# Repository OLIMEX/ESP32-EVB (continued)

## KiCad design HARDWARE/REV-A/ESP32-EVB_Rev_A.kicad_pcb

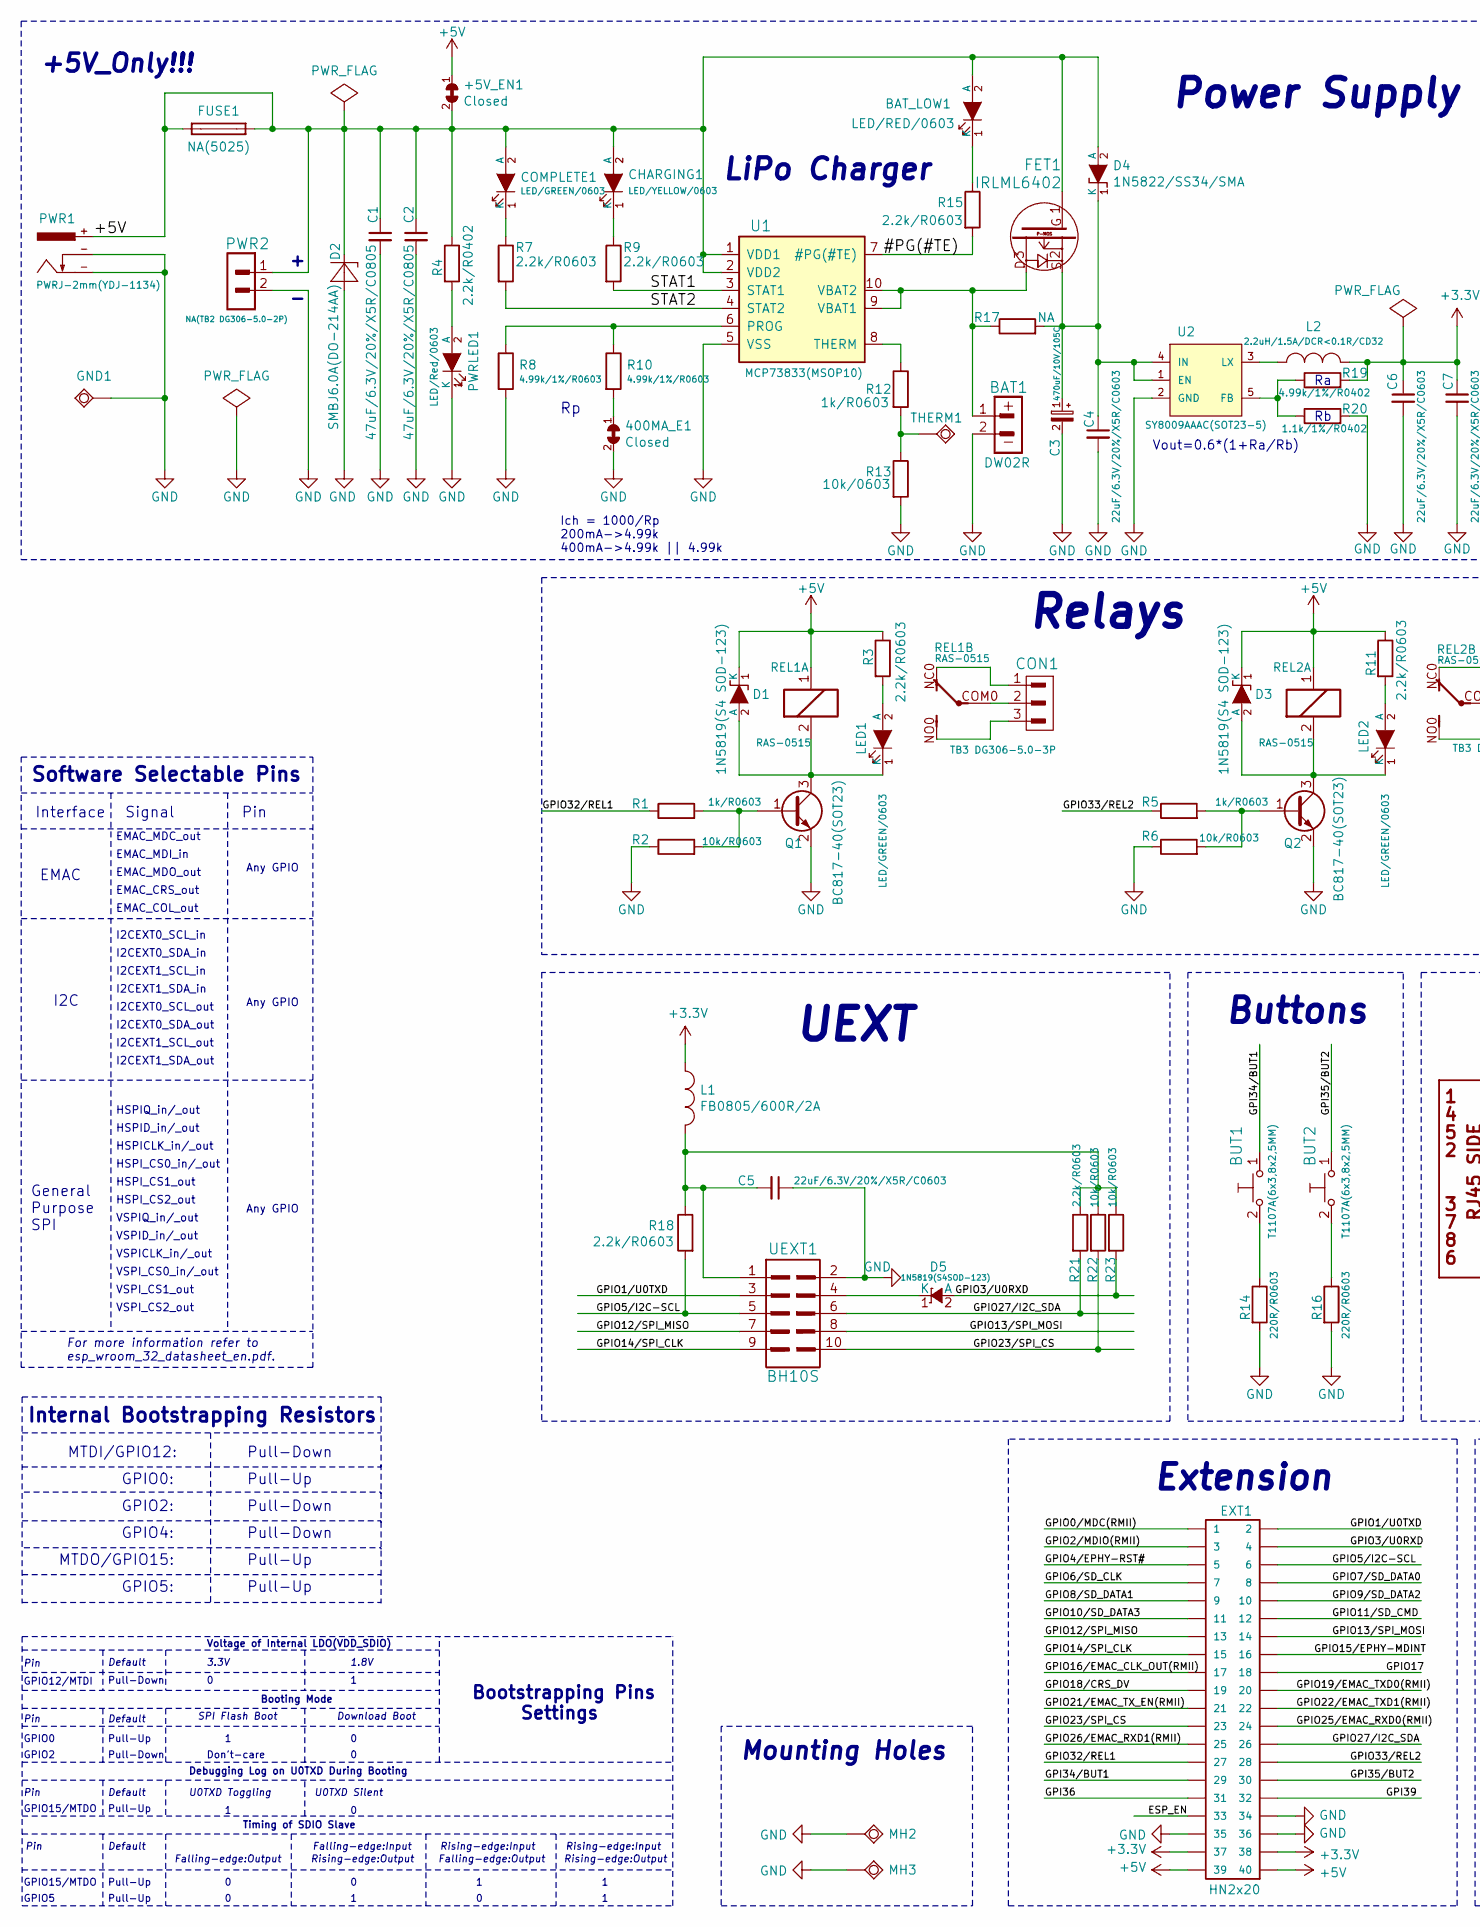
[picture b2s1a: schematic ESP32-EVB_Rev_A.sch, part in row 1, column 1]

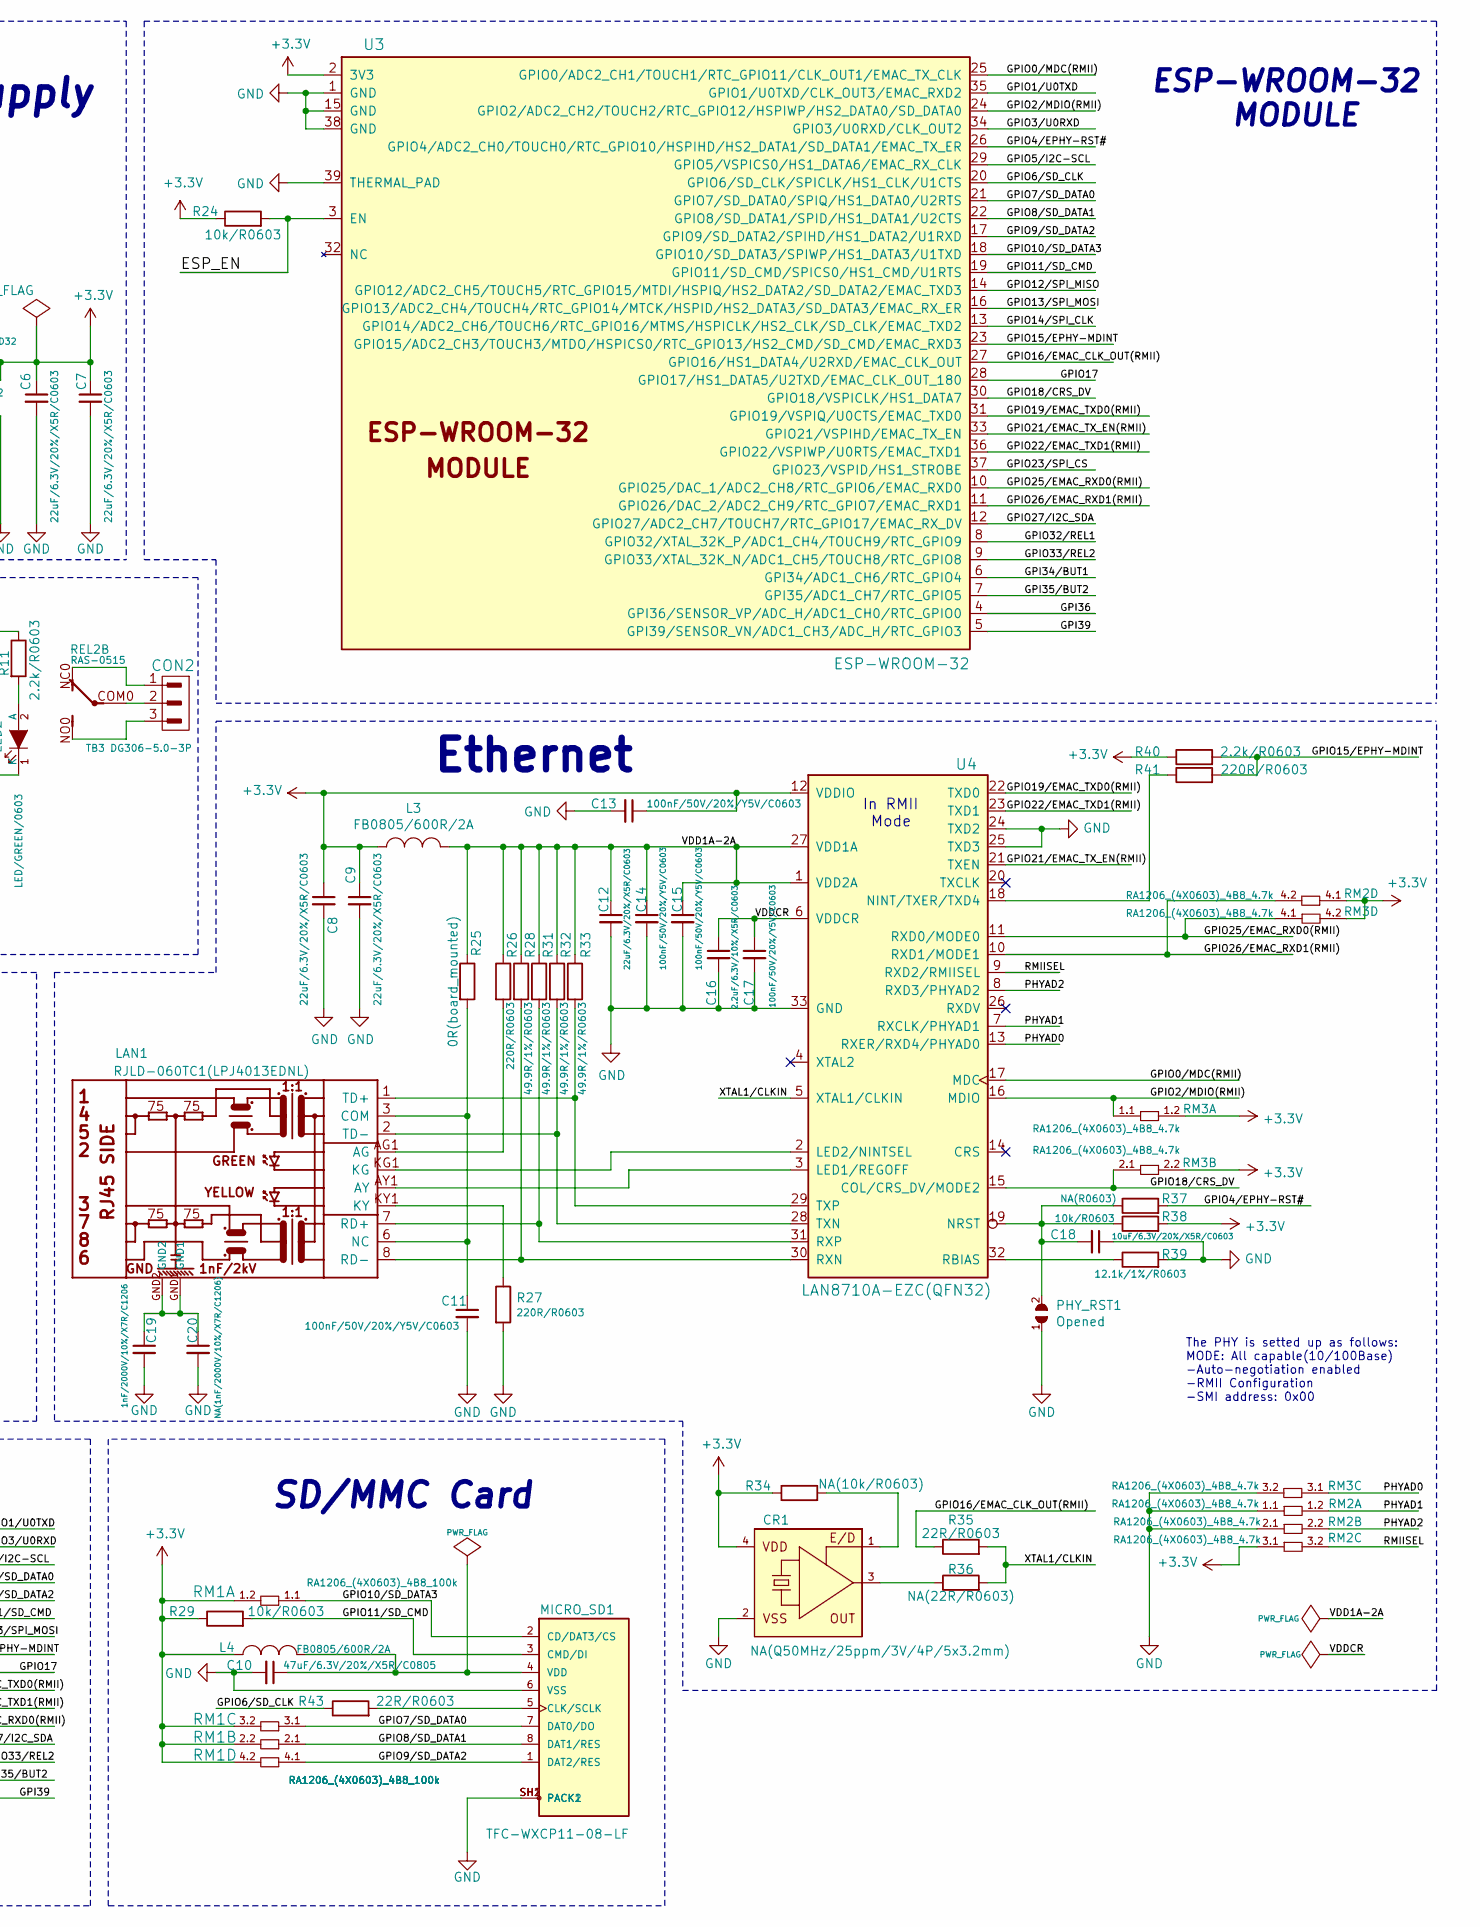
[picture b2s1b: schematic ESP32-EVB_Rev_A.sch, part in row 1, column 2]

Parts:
400MA_E1: Closed; SJ_Closed
+5V_EN1: Closed; SJ_Closed
BAT1: DW02R; LIPO_BAT-CON2DW02R
BAT_LOW1: LED/RED/0603; LED_0603_KA
BUT1, BUT2: T1107A(6x3,8x2,5MM)
C1, C2, C10: 47uF/6.3V/20%/X5R/C0805; C_0805_5MIL_DWS
C3: 470uF/10V/105C; CPOL-EUE2.5-6.3(CPOL-EU)
C4, C5, C6, C7, C8, C9, C12: 22uF/6.3V/20%/X5R/C0603; C_0603_5MIL_DWS
C11, C13, C14, C15, C17: 100nF/50V/20%/Y5V/C0603; C_0603_5MIL_DWS
C16: 2.2uF/6.3V/10%/X5R/C0603; C_0603_5MIL_DWS
C18: 10uF/6.3V/20%/X5R/C0603; C_0603_5MIL_DWS
C19: 1nF/2000V/10%/X7R/C1206; C_1206_5MIL_DWS_ISO
C20: NA(1nF/2000V/10%/X7R/C1206); C_1206_5MIL_DWS_ISO
CHARGING1: LED/YELLOW/0603; LED_0603_KA
COMPLETE1: LED/GREEN/0603; LED_0603_KA
CON1, CON2: TB3 DG306-5.0-3P; TB3-DG306-5.0_3P
CR1: NA(Q50MHz/25ppm/3V/4P/5x3.2mm); 5032-4P_HCX-3S
D1, D3: 1N5819(S4 SOD-123); SOD-123_1C-2A_KA
D2: SMBJ6.0A(DO-214AA); DO214AA
D4: 1N5822/SS34/SMA; SMA-KA
D5: 1N5819(S4SOD-123); SOD-123_1C-2A_KA
EXT1: HN2x20
FET1: IRLML6402; SOT23
FUSE1: NA(5025); FUSE-5025
GND1: TESTPAD; TESTPAD_40-ROUND
L1, L3, L4: FB0805/600R/2A; L_0805_5MIL_DWS
L2: 2.2uH/1.5A/DCR<0.1R/CD32; CD32
LAN1: RJLD-060TC1(LPJ4013EDNL); RJLBC-060TC1
LED1, LED2: LED/GREEN/0603; LED_0603_KA
MH2, MH3: Mounting_hole_Shield_3.3mm
MICRO_SD1: TFC-WXCP11-08-LF
PHY_RST1: Opened; SJ
PWR1: PWRJ-2mm(YDJ-1134); PWRJ-2mm(YDJ-1136)
PWR2: NA(TB2 DG306-5.0-2P); TB2-DG306-5.0_2P
PWRLED1: LED/Red/0603; LED_0603_KA
Q1, Q2: BC817-40(SOT23); SOT23
R1, R5, R12: 1k/R0603; R_0603_5MIL_DWS
R2, R6, R22, R23, R24, R29, R38: 10k/R0603; R_0603_5MIL_DWS
R3, R7, R9, R11, R15, R18, R21, R40: 2.2k/R0603; R_0603_5MIL_DWS
R4: 2.2k/R0402; R_0402_5MIL_DWS
R8, R10: 4.99k/1%/R0603; R_0603_5MIL_DWS
R13: 10k/0603; R_0603_5MIL_DWS
R14, R16, R26, R27, R41: 220R/R0603; R_0603_5MIL_DWS
R17: NA; R_0603_5MIL_DWS
R19: 4.99k/1%/R0402; R_0402_5MIL_DWS
R20: 1.1k/1%/R0402; R_0402_5MIL_DWS
R25: 0R(board_mounted); 0R_0603
R28, R31, R32, R33: 49.9R/1%/R0603; R_0603_5MIL_DWS
R34: NA(10k/R0603); R_0603_5MIL_DWS
R35, R43: 22R/R0603; R_0603_5MIL_DWS
R36: NA(22R/R0603); R_0603_5MIL_DWS
R37: NA(R0603); R_0603_5MIL_DWS
R39: 12.1k/1%/R0603; R_0603_5MIL_DWS
REL1, REL2: RAS-0515; Relay_RAS-05-15
RM1: RA1206_(4X0603)_4B8_100k; R_MATRIX_4
RM2, RM3: RA1206_(4X0603)_4B8_4.7k; R_MATRIX_4
THERM1: TESTPAD; TESTPAD_40-ROUND
U1: MCP73833(MSOP10); MSOP-10_Pitch-0.5mm_3.00x3.00x1.00mm
U2: SY8009AAAC(SOT23-5); SOT-23-5
U3: ESP-WROOM-32; ESP-WROOM-32_MODULE
U4: LAN8710A-EZC(QFN32); QFN32_EP(33)_5.00x5.00x0.90mm_Pitch_0.50mm
UEXT1: BH10S; UEXT_ML10

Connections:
+3V3: C6.1, C7.1, C8.1, C9.1, C13.1, CR1.4 (VDD), EXT1.37, EXT1.38, L1.1, L2.2, L3.1, L4.1, R19.2, R24.1, R29.1, R34.1, R38.2, R40.1, RM1.1.2, RM1.2.2, RM1.3.2, RM1.4.2, RM2.3.1, RM2.4.1, RM3.1.2, RM3.2.2, RM3.4.2, U3.2 (3V3), U4.12 (VDDIO)
+5V: +5V_EN1.1, +5V_EN1.2, BAT_LOW1.2 (A), C1.1, C2.1, CHARGING1.2 (A), COMPLETE1.2 (A), D1.1 (K), D2.C, D3.1 (K), D4.2 (A), EXT1.39, EXT1.40, FET1.1, FUSE1.1, FUSE1.2, PWR1.+, PWR2.1, R3.1, R4.1, R11.1, REL1.1, REL2.1, U1.1 (VDD1), U1.2 (VDD2)
/#PG(#TE): R15.2, U1.7 (#PG(#TE))
/ESP_EN: EXT1.33, R24.2, U3.3 (EN)
/GPI34/BUT1: BUT1.1, EXT1.29, U3.6 (GPI34/ADC1_CH6/RTC_GPIO4)
/GPI35/BUT2: BUT2.1, EXT1.30, U3.7 (GPI35/ADC1_CH7/RTC_GPIO5)
/GPI36: EXT1.31, U3.4 (GPI36/SENSOR_VP/ADC_H/ADC1_CH0/RTC_GPIO0)
/GPI39: EXT1.32, U3.5 (GPI39/SENSOR_VN/ADC1_CH3/ADC_H/RTC_GPIO3)
/GPIO0/MDC(RMII): EXT1.1, U3.25 (GPIO0/ADC2_CH1/TOUCH1/RTC_GPIO11/CLK_OU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), U4.17 (MDC)
/GPIO1/U0TXD: EXT1.2, U3.35 (GPIO1/U0TXD/CLK_OUT3/EMAC_RXD2), UEXT1.3
/GPIO2/MDIO(RMII): EXT1.3, RM3.1.1, U3.24 (GPIO2/ADC2_CH2/TOUCH2/RTC_GPIO12/HSPIWP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), U4.16 (MDIO)
/GPIO3/U0RXD: D5.2 (A), EXT1.4, R23.2, U3.34 (GPIO3/U0RXD/CLK_OUT2)
/GPIO4/EPHY-RST#: EXT1.5, R37.2, U3.26 (GPIO4/ADC2_CH0/TOUCH0/RTC_GPIO10/HSPIHD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)
/GPIO5/I2C-SCL: EXT1.6, R18.2, U3.29 (GPIO5/VSPICS0/HS1_DATA6/EMAC_RX_CLK), UEXT1.5
/GPIO6/SD_CLK: EXT1.7, R43.1, U3.20 (GPIO6/SD_CLK/SPICLK/HS1_CLK/U1CTS)
/GPIO7/SD_DATA0: EXT1.8, MICRO_SD1.7 (DAT0/DO), RM1.3.1, U3.21 (GPIO7/SD_DATA0/SPIQ/HS1_DATA0/U2RTS)
/GPIO8/SD_DATA1: EXT1.9, MICRO_SD1.8 (DAT1/RES), RM1.2.1, U3.22 (GPIO8/SD_DATA1/SPID/HS1_DATA1/U2CTS)
/GPIO9/SD_DATA2: EXT1.10, MICRO_SD1.1 (DAT2/RES), RM1.4.1, U3.17 (GPIO9/SD_DATA2/SPIHD/HS1_DATA2/U1RXD)
/GPIO10/SD_DATA3: EXT1.11, MICRO_SD1.2 (CD/DAT3/CS), RM1.1.1, U3.18 (GPIO10/SD_DATA3/SPIWP/HS1_DATA3/U1TXD)
/GPIO11/SD_CMD: EXT1.12, MICRO_SD1.3 (CMD/DI), R29.2, U3.19 (GPIO11/SD_CMD/SPICS0/HS1_CMD/U1RTS)
/GPIO12/SPI_MISO: EXT1.13, U3.14 (GPIO12/ADC2_CH5/TOUCH5/RTC_GPIO15/MTDI/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), UEXT1.7
/GPIO13/SPI_MOSI: EXT1.14, U3.16 (GPIO13/ADC2_CH4/TOUCH4/RTC_GPIO14/MTCK/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), UEXT1.8
/GPIO14/SPI_CLK: EXT1.15, U3.13 (GPIO14/ADC2_CH6/TOUCH6/RTC_GPIO16/MTMS/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), UEXT1.9
/GPIO15/EPHY-MDINT: EXT1.16, R40.2, R41.2, U3.23 (GPIO15/ADC2_CH3/TOUCH3/MTDO/HSPICS0/RTC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)
/GPIO16/EMAC_CLK_OUT(RMII): EXT1.17, R35.1, U3.27 (GPIO16/HS1_DATA4/U2RXD/EMAC_CLK_OUT)
/GPIO17: EXT1.18, U3.28 (GPIO17/HS1_DATA5/U2TXD/EMAC_CLK_OUT_180)
/GPIO18/CRS_DV: EXT1.19, RM3.2.1, U3.30 (GPIO18/VSPICLK/HS1_DATA7), U4.15 (COL/CRS_DV/MODE2)
/GPIO19/EMAC_TXD0(RMII): EXT1.20, U3.31 (GPIO19/VSPIQ/U0CTS/EMAC_TXD0), U4.22 (TXD0)
/GPIO21/EMAC_TX_EN(RMII): EXT1.21, U3.33 (GPIO21/VSPIHD/EMAC_TX_EN), U4.21 (TXEN)
/GPIO22/EMAC_TXD1(RMII): EXT1.22, U3.36 (GPIO22/VSPIWP/U0RTS/EMAC_TXD1), U4.23 (TXD1)
/GPIO23/SPI_CS: EXT1.23, R22.2, U3.37 (GPIO23/VSPID/HS1_STROBE), UEXT1.10
/GPIO25/EMAC_RXD0(RMII): EXT1.24, RM3.4.1, U3.10 (GPIO25/DAC_1/ADC2_CH8/RTC_GPIO6/EMAC_RX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), U4.11 (RXD0/MODE0)
/GPIO26/EMAC_RXD1(RMII): EXT1.25, RM2.4.2, U3.11 (GPIO26/DAC_2/ADC2_CH9/RTC_GPIO7/EMAC_RX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), U4.10 (RXD1/MODE1)
/GPIO27/I2C_SDA: EXT1.26, R21.2, U3.12 (GPIO27/ADC2_CH7/TOUCH7/RTC_GPIO17/EMAC_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), UEXT1.6
/GPIO32/REL1: EXT1.27, R1.1, U3.8 (GPIO32/XTAL_32K_P/ADC1_CH4/TOUCH9/RTC_G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)
/GPIO33/REL2: EXT1.28, R5.1, U3.9 (GPIO33/XTAL_32K_N/ADC1_CH5/TOUCH8/RTC_G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)
/PHYAD0: RM3.3.1, U4.13 (RXER/RXD4/PHYAD0)
/PHYAD1: RM2.1.2, U4.7 (RXCLK/PHYAD1)
/PHYAD2: RM2.2.2, U4.8 (RXD3/PHYAD2)
/RMIISEL: RM2.3.2, U4.9 (RXD2/RMIISEL)
/STAT1: R9.2, U1.3 (STAT1)
/STAT2: R7.2, U1.4 (STAT2)
/VDD1A-2A: C12.1, C14.1, C15.1, L3.2, R25.1, R26.1, R28.1, R31.1, R32.1, R33.1, U4.1 (VDD2A), U4.27 (VDD1A)
/VDDCR: C16.1, C17.1, U4.6 (VDDCR)
/XTAL1/CLKIN: R35.2, R36.2, U4.5 (XTAL1/CLKIN)
GND: 400MA_E1.2, BAT1.2, C1.2, C2.2, C3.2 (-), C4.2, C5.1, C6.2, C7.2, C8.2, C9.2, C10.2, C11.2, C12.2, C13.2, C14.2, C15.2, C16.2, C17.2, C18.1, C19.2, C20.2, CR1.2 (VSS), D2.A, EXT1.34, EXT1.35, EXT1.36, GND1.1, MH2.GND1, MH3.GND1, MICRO_SD1.6 (VSS), MICRO_SD1.SH1 (PACK1), MICRO_SD1.SH2 (PACK2), PHY_RST1.1, PWR1.-, PWR2.2, PWRLED1.1 (K), Q1.2 (E), Q2.2 (E), R2.1, R6.1, R8.2, R13.2, R14.2, R16.2, R20.2, R27.2, R39.2, RM2.1.1, RM2.2.1, RM3.3.2, U1.5 (VSS), U2.2 (GND), U3.1 (GND), U3.15 (GND), U3.38 (GND), U3.39 (THERMAL_PAD), U4.24 (TXD2), U4.25 (TXD3), U4.33 (GND), UEXT1.2
unnamed: 400MA_E1.1, R10.2
unnamed: BAT1.1, FET1.3, R17.1, U1.9 (VBAT1), U1.10 (VBAT2)
unnamed: BAT_LOW1.1 (K), R15.1
unnamed: BUT1.2, R14.1
unnamed: BUT2.2, R16.1
unnamed: C3.1 (+), C4.1, D4.1 (K), FET1.2, R17.2, U2.1 (EN), U2.4 (IN)
unnamed: C5.2, L1.2, R18.1, R21.1, R22.1, R23.1, UEXT1.1
unnamed: C10.1, L4.2, MICRO_SD1.4 (VDD)
unnamed: C11.1, LAN1.3 (COM), LAN1.6 (NC), R25.2
unnamed: C18.2, PHY_RST1.2, R37.1, R38.1, U4.19 (NRST)
unnamed: C19.1, C20.1, LAN1.GND1, LAN1.GND2
unnamed: CHARGING1.1 (K), R9.1
unnamed: COMPLETE1.1 (K), R7.1
unnamed: CON1.1, REL1.NC0
unnamed: CON1.2, REL1.COM0
unnamed: CON1.3, REL1.NO0
unnamed: CON2.1, REL2.NC0
unnamed: CON2.2, REL2.COM0
unnamed: CON2.3, REL2.NO0
unnamed: CR1.1 (E/D), R34.2
unnamed: CR1.3 (OUT), R36.1
unnamed: D1.2 (A), LED1.1 (K), Q1.3 (C), REL1.2
unnamed: D3.2 (A), LED2.1 (K), Q2.3 (C), REL2.2
unnamed: D5.1 (K), UEXT1.4
unnamed: L2.1, U2.3 (LX)
unnamed: LAN1.1 (TD+), R33.2, U4.29 (TXP)
unnamed: LAN1.2 (TD-), R32.2, U4.28 (TXN)
unnamed: LAN1.7 (RD+), R31.2, U4.31 (RXP)
unnamed: LAN1.8 (RD-), R28.2, U4.30 (RXN)
unnamed: LAN1.AG1 (AG), R26.2
unnamed: LAN1.AY1 (AY), U4.3 (LED1/REGOFF)
unnamed: LAN1.KG1 (KG), U4.2 (LED2/NINTSEL)
unnamed: LAN1.KY1 (KY), R27.1
unnamed: LED1.2 (A), R3.2
unnamed: LED2.2 (A), R11.2
unnamed: MICRO_SD1.5 (CLK/SCLK), R43.2
unnamed: PWRLED1.2 (A), R4.2
unnamed: Q1.1 (B), R1.2, R2.2
unnamed: Q2.1 (B), R5.2, R6.2
unnamed: R8.1, R10.1, U1.6 (PROG)
unnamed: R12.1, U1.8 (THERM)
unnamed: R12.2, R13.1, THERM1.1
unnamed: R19.1, R20.1, U2.5 (FB)
unnamed: R39.1, U4.32 (RBIAS)
unnamed: R41.1, U4.18 (NINT/TXER/TXD4)

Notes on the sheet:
Vout=0.6*(1+Ra/Rb)
Power Supply
Buttons
Relays
UEXT
Ich = 1000/Rp 200mA->4.99k 400mA->4.99k || 4.99k
In RMII Mode
Ethernet
ESP-WROOM-32 MODULE
SD/MMC Card
Bootstrapping Pins Settings
Internal Bootstrapping Resistors
MTDI/GPIO12:
Pull-Down
GPIO0:
Pull-Up
GPIO2:
GPIO4:
MTDO/GPIO15:
GPIO5:
Voltage of Internal LDO(VDD_SDIO)
Pin
Default
3.3V
1.8V
Booting Mode
GPIO12/MTDI
GPIO0
GPIO2
SPI Flash Boot
Download Boot
Don't-care
Debugging Log on U0TXD During Booting
U0TXD Toggling
U0TXD Silent
GPIO15/MTDO
Timing of SDIO Slave
For more information refer to esp_wroom_32_datasheet_en.pdf.
Falling-edge:Output
Falling-edge:Input

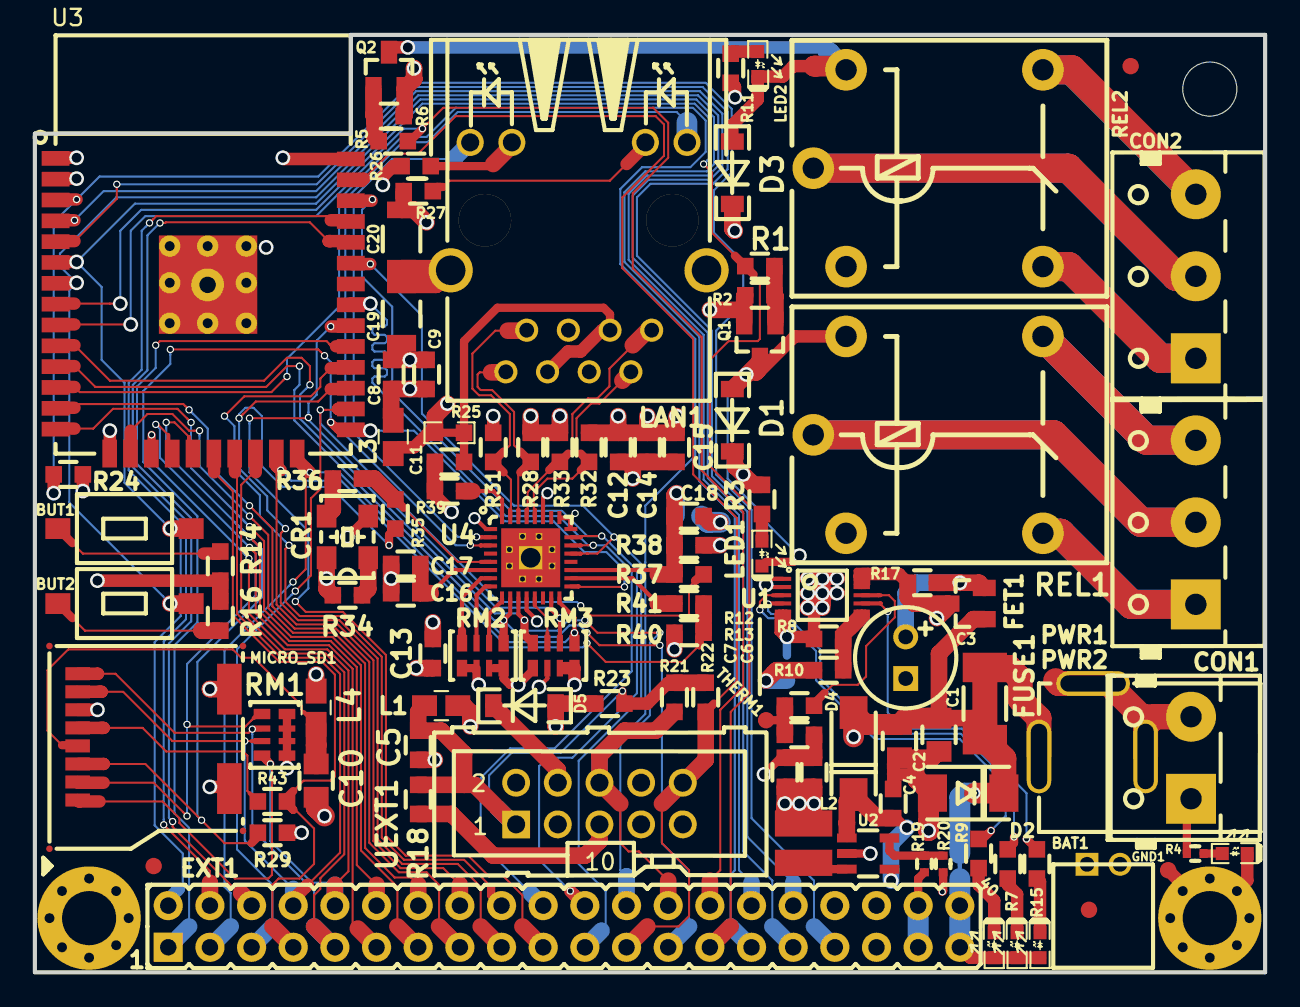
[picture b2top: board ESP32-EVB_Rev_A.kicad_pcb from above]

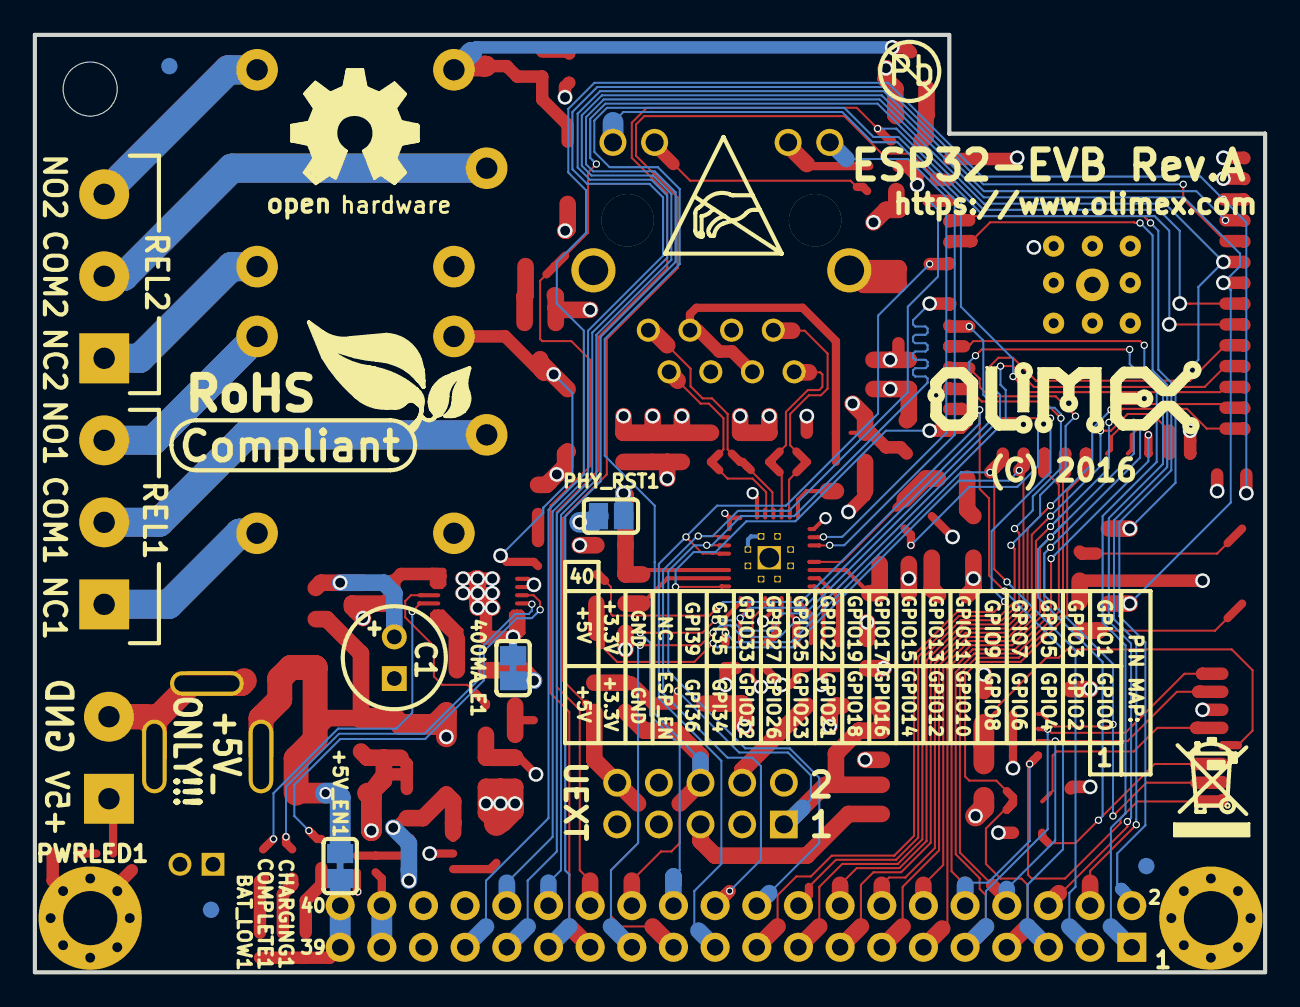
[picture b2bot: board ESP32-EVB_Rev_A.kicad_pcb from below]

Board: 4 copper layers, 75.0 x 57.2 mm, 111 parts (5 on the bottom side), 91 nets.

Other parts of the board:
MH1: Mounting_hole_Shield_3.3mm; Mounting_hole_3.3mm
Ref**: Val**; LOGO_ANTISTATIC_1
Ref**#2: Val**; LOGO_ROHS_1

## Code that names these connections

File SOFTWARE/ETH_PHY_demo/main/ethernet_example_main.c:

/* ethernet Example

   This example code is in the Public Domain (or CC0 licensed, at your option.)

   Unless required by applicable law or agreed to in writing, this
   software is distributed on an "AS IS" BASIS, WITHOUT WARRANTIES OR
   CONDITIONS OF ANY KIND, either express or implied.

   2017 June 15 rudi ;-)
   change log
   edit ETH PHY Example for ESP32 EVB REV B IoT LAN8710 Board with CAN
   - Board use LAN8710 without OSC Power Enable PIN
   - - TLK110 was removed
   - - Kconfig menuconfig TLK110 entry removed cause not need here
   - - we use LAN8720 config for the LAN8710 ( compatible )
   - - Power PIN was not used in shematic and board so not used in code
   - -


*/
#include <stdio.h>
#include <string.h>

#include "freertos/FreeRTOS.h"
#include "freertos/task.h"

#include "esp_system.h"
#include "esp_err.h"
#include "esp_event_loop.h"
#include "esp_event.h"
#include "esp_attr.h"
#include "esp_log.h"
#include "esp_eth.h"

#include "rom/ets_sys.h"
#include "rom/gpio.h"

#include "soc/dport_reg.h"
#include "soc/io_mux_reg.h"
#include "soc/rtc_cntl_reg.h"
#include "soc/gpio_reg.h"
#include "soc/gpio_sig_map.h"

#include "tcpip_adapter.h"
#include "nvs_flash.h"
#include "driver/gpio.h"

#include "eth_phy/phy_lan8720.h"
#define DEFAULT_ETHERNET_PHY_CONFIG phy_lan8720_default_ethernet_config

static const char *TAG = "Olimex_ESP32_EVB_REV_B_eth_example";

// not need here in this Board Configuration
// #define PIN_PHY_POWER CONFIG_PHY_POWER_PIN
#define PIN_SMI_MDC   CONFIG_PHY_SMI_MDC_PIN
#define PIN_SMI_MDIO  CONFIG_PHY_SMI_MDIO_PIN


static void eth_gpio_config_rmii(void)
{
    // RMII data pins are fixed:
    // TXD0 = GPIO19
    // TXD1 = GPIO22
    // TX_EN = GPIO21
    // RXD0 = GPIO25
    // RXD1 = GPIO26
    // CLK == GPIO0
    phy_rmii_configure_data_interface_pins();
    // MDC is GPIO 23, MDIO is GPIO 18
    phy_rmii_smi_configure_pins(PIN_SMI_MDC, PIN_SMI_MDIO);
}

void eth_task(void *pvParameter)
{
    tcpip_adapter_ip_info_t ip;
    memset(&ip, 0, sizeof(tcpip_adapter_ip_info_t));
    vTaskDelay(2000 / portTICK_PERIOD_MS);

    while (1) {

        vTaskDelay(2000 / portTICK_PERIOD_MS);

        if (tcpip_adapter_get_ip_info(ESP_IF_ETH, &ip) == 0) {
        	ESP_LOGI(TAG, "~~~~~~~~~~~");
            ESP_LOGI(TAG, "ETHIP:"IPSTR, IP2STR(&ip.ip));
            ESP_LOGI(TAG, "ETHPMASK:"IPSTR, IP2STR(&ip.netmask));
            ESP_LOGI(TAG, "ETHPGW:"IPSTR, IP2STR(&ip.gw));
            ESP_LOGI(TAG, "~~~~~~~~~~~");
        }
    }
}

void app_main()
{
    esp_err_t ret = ESP_OK;
    tcpip_adapter_init();
    esp_event_loop_init(NULL, NULL);

    eth_config_t config = DEFAULT_ETHERNET_PHY_CONFIG;
    /* Set the PHY address in the example configuration */
    config.phy_addr = CONFIG_PHY_ADDRESS;
    config.gpio_config = eth_gpio_config_rmii;
    config.tcpip_input = tcpip_adapter_eth_input;

    ret = esp_eth_init(&config);

    if(ret == ESP_OK) {
        esp_eth_enable();
        xTaskCreate(eth_task, "eth_task", 2048, NULL, (tskIDLE_PRIORITY + 2), NULL);
    }

}

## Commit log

2017-02-10 Initial REV-A hardware
2017-05-29 ESP32-EVB revision B update
2017-06-02 Uploaded toggle_relay example
2017-06-14 Add CAN Demo for the EVB Rev B
    Demo CAN
    ESP32 EVB REV B provide CAN on
    Rx GPIO 35
    Tx GPIO 5
    You can set over kconfig CAN properties.
    We send with NODE 0xC5 standard frames with 8 byte and
2017-06-15 update
    project tag changed to CAN-DEMO
2017-06-15 Add ETH PHY Demo for the EVB Rev B
    Demo ETH PHY
    ESP32 EVB REV B provide ETH PHY with LAN8710
    we use for config the compatible LAN8720 config
    the demo code was revised for EVB REV B
    TLK110 option was removed, also the PHY Power enable
    is not need on the EVB REV B Board.
2017-06-15 Add ETH PHY Demo for the EVB Rev B
2017-07-12 Added SD card example
2017-10-23 Update
    hardware revision C files
2017-12-07 add WATERING project
2018-03-21 New demo
    esp32-evb with mod-rtc
2018-03-22 New demo
    New demo of ESP32-EVB and MOD-OLED
2018-03-27 fix
    Small typo in the comments about I2C pins
2018-07-04 Fix
    Changed ethernet example
2019-06-13 Added demo
    Added ESP32-EVB iperf demo.
2020-07-16 Added example
    Added ethernet example for ESP-IDF 4.0 and 4.0.1
2020-07-27 Update
    Revision I added, revision changes updated
2021-10-13 Update
    Dimensions
2022-02-11 Update
    Updated a couple of examples for ESP-IDF v4.4, cleaned the repo a bit
2022-03-25 Tailor to ESP32-EVB
    Combined "Pin Assignment" and "Configure the project" sections and provided ESP32-EVB-specific values.
2022-03-29 Initial commit. WIP.
    Work in progress for CAN example.
2022-03-29 Completed example
2022-03-29 Revert "merge CAN example"
    This reverts commit 4bf0b1a2a6c90895a12588282d1a981c095b3d41.
2022-04-11 working example
    working example, but in test it drifted 10 minutes over 60 hours. Assumes a 20x4 LCD in 4-bit parallel mode.
2022-04-11 cleaned artifacts
2022-04-19 SX109 proof of concept
    there's a loss of frass in here, too
2022-05-11 New example
    Added MOD-IO2 example
2022-05-18 Example addition
    Added CAN library and examples for Arduino IDE
2022-05-19 Update
    Added CAN example for IDF
2022-07-27 Update
    Added info on Arduino for ESP32 installation.
2023-07-07 Update
    Revision K1
2023-07-24 toggle_relay
2023-07-24 make working
2023-07-24 sd_card on esp-idf-v5.0.2
2023-11-13 New example
    Added new ethernet example for esp-idf 5.1.1
2023-11-29 Update
    MQQT examples ESP32-EVB
2024-08-28 Update
    Manual
2025-10-21 Update
    Added revisions K2 and L.
2026-01-16 Update
    box design
